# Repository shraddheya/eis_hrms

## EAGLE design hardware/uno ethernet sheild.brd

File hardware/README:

Hardware and firmware goes here

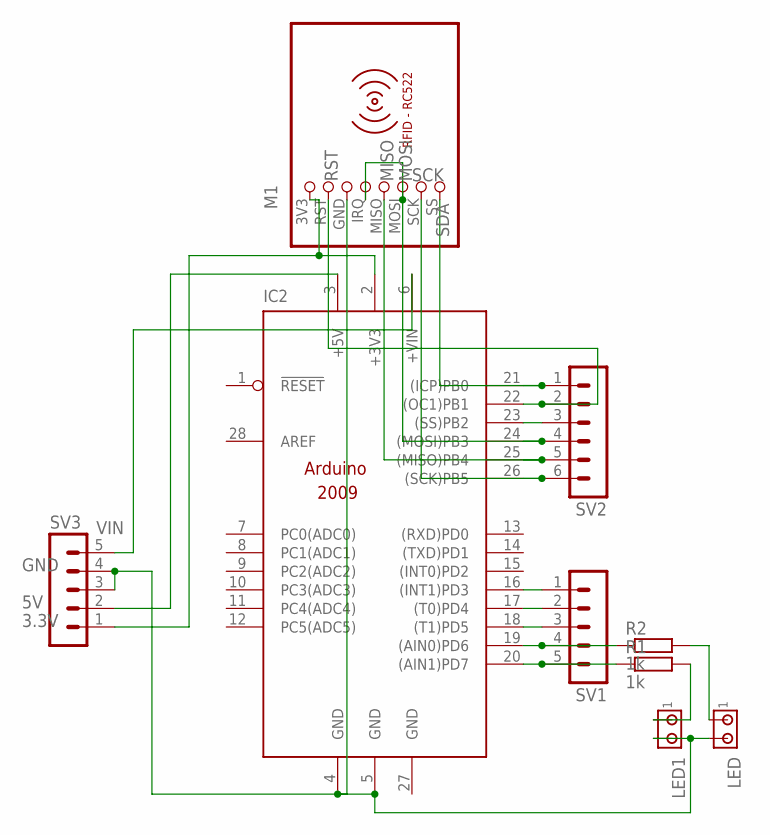
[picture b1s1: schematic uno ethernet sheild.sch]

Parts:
IC2: ARDUINO2009_PIN_12; ARDUINO2009_2
LED, LED1: MTA02-100; 10X02MTA
M1: RFID-RC522
R1, R2: 1k; 0207/10
SV1, SV3: MA05-1
SV2: MA06-1

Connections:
3.3V: IC2.2 (+3V3), M1.3V3 (1), SV3.1
5V: IC2.3 (+5V), SV3.2
GND: IC2.4 (GND), IC2.5 (GND), IC2.27 (GND), LED.2, LED1.2, M1.GND (3), SV3.3, SV3.4
MISO: IC2.25 ((MISO)PB4), M1.MISO (5), SV2.5
MOSI: IC2.24 ((MOSI)PB3), M1.IRQ (4), M1.MOSI (6), SV2.4
unnamed: LED1.1, R1.2
unnamed: LED.1, R2.2
unnamed: IC2.20 ((AIN1)PD7), R1.1, SV1.5
unnamed: IC2.19 ((AIN0)PD6), R2.1, SV1.4
unnamed: IC2.18 ((T1)PD5), SV1.3
unnamed: IC2.17 ((T0)PD4), SV1.2
unnamed: IC2.16 ((INT1)PD3), SV1.1
unnamed: IC2.23 ((SS)PB2), SV2.3
RST: IC2.22 ((OC1)PB1), M1.RST (2), SV2.2
SCK: IC2.26 ((SCK)PB5), M1.SCK (7), SV2.6
SDA: IC2.21 ((ICP)PB0), M1.SS (8), SV2.1
VIN: IC2.6 (+VIN), SV3.5

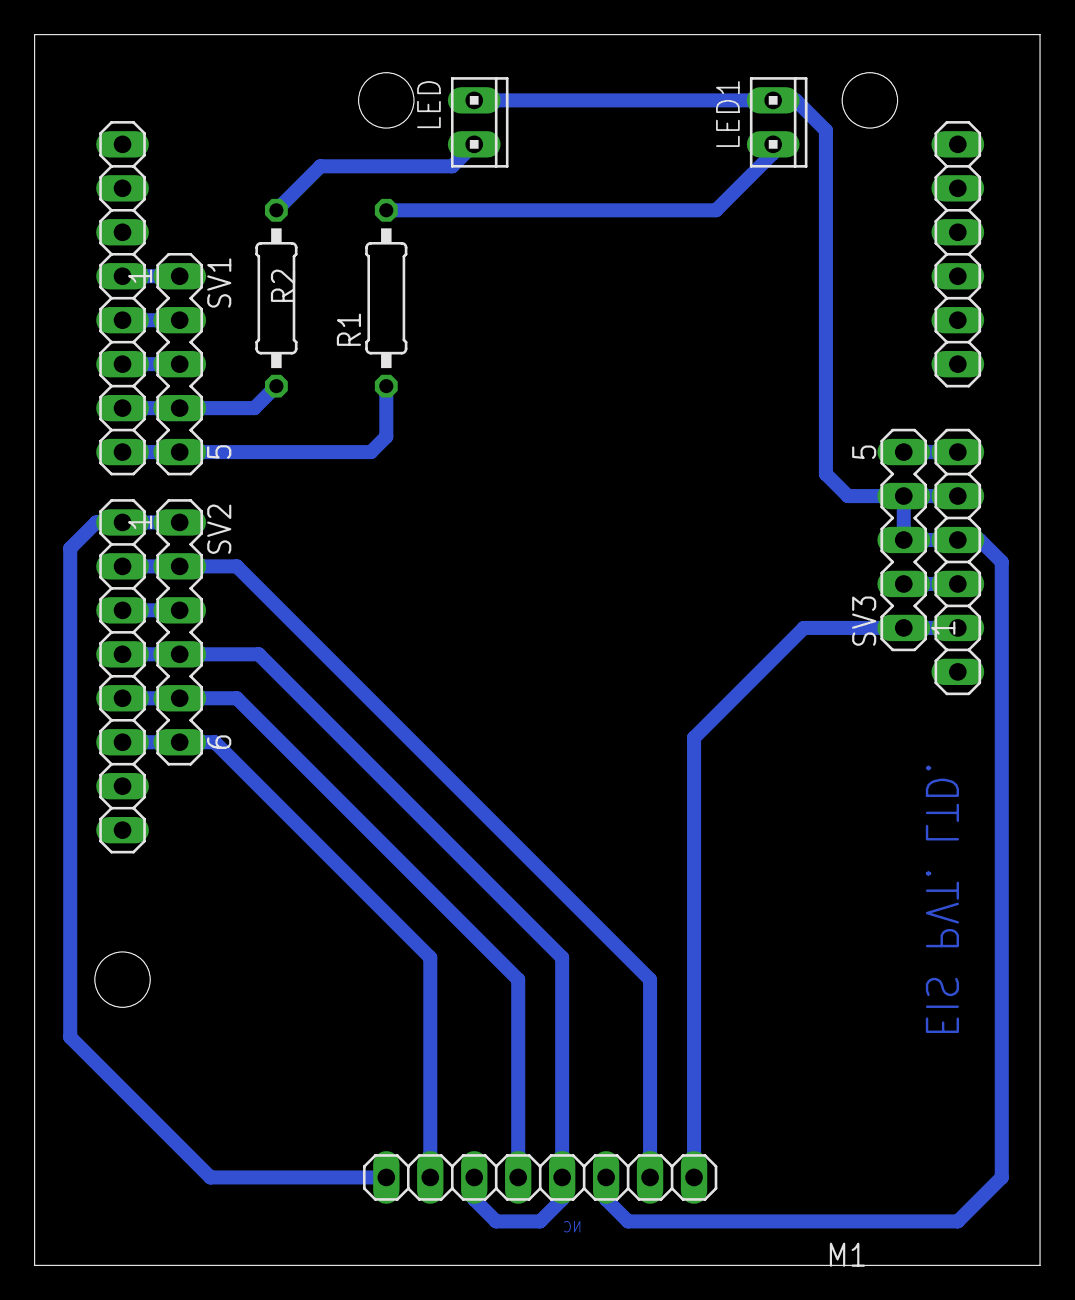
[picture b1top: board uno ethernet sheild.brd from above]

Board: 2 copper layers, 58.1 x 71.1 mm, 9 parts (0 on the bottom side), 17 nets.

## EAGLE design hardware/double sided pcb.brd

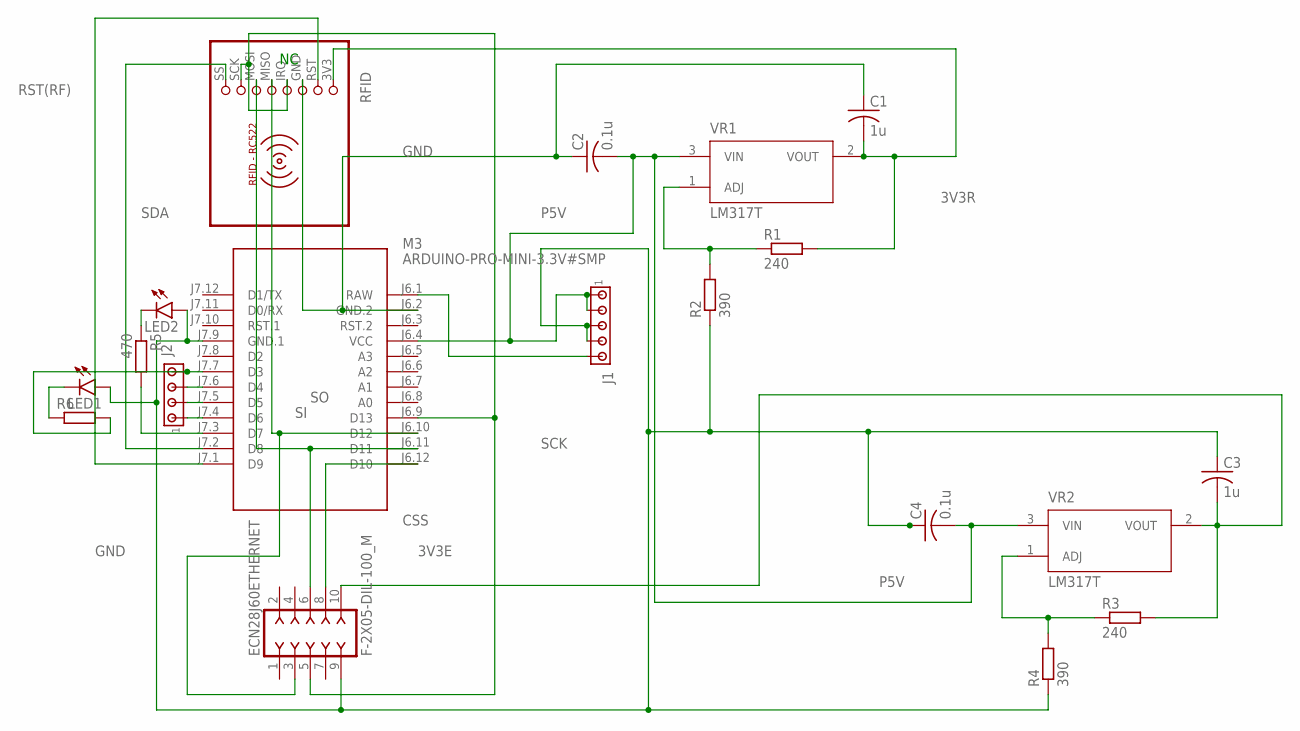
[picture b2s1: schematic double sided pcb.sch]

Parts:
C1, C3: 1u; C025-025X050
C2, C4: 0.1u; C025-025X050
ECN28J60ETHERNET: F-2X05-DIL-100_M; DIL-100-2X05_M
J1: MTA05-100; 10X05MTA
J2: MTA04-100; 10X04MTA
LED1, LED2: LED3MM
M3: ARDUINO-PRO-MINI-3.3V#SMP; ARDUINO-PRO-MINI#SMP
R1, R3: 240; 0207/10
R2, R4: 390; 0207/10
R5: 470; 0207/10
R6: R-EU_0207/10; 0207/10
RFID: RFID-RC522
VR1, VR2: LM317T; TO254P1054X470X1955-3

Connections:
3V3E: C3.2, ECN28J60ETHERNET.10, R3.2, VR2.2 (VOUT)
3V3R: C1.2, R1.2, RFID.3V3 (1), VR1.2 (VOUT)
9V: J1.5, M3.J6.1 (RAW)
CSS: ECN28J60ETHERNET.8, M3.J6.12 (D10)
GND: C1.1, C2.1, C3.1, C4.1, ECN28J60ETHERNET.9, J1.3, J1.4, LED1.A, LED2.A, M3.J6.2 (GND.2), M3.J7.9 (GND.1), R2.1, R4.1, RFID.GND (3)
unnamed: R1.1, R2.2, VR1.1 (ADJ)
unnamed: R3.1, R4.2, VR2.1 (ADJ)
unnamed: J2.3, M3.J7.6 (D4)
unnamed: LED2.K (C), R5.1
unnamed: M3.J7.3 (D7), R5.2
unnamed: J2.1, M3.J7.4 (D6)
unnamed: J2.2, M3.J7.5 (D5)
unnamed: J2.4, M3.J7.7 (D3), R6.2
unnamed: LED1.K (C), R6.1
P5V: C2.2, C4.2, J1.1, J1.2, M3.J6.4 (VCC), VR1.3 (VIN), VR2.3 (VIN)
RST(RF): M3.J7.1 (D9), RFID.RST (2)
SCK: ECN28J60ETHERNET.5, M3.J6.9 (D13), RFID.IRQ (4), RFID.SCK (7)
SDA: M3.J7.2 (D8), RFID.SS (8)
SI: ECN28J60ETHERNET.6, M3.J6.11 (D11), RFID.MOSI (6)
SO: ECN28J60ETHERNET.3, M3.J6.10 (D12), RFID.MISO (5)

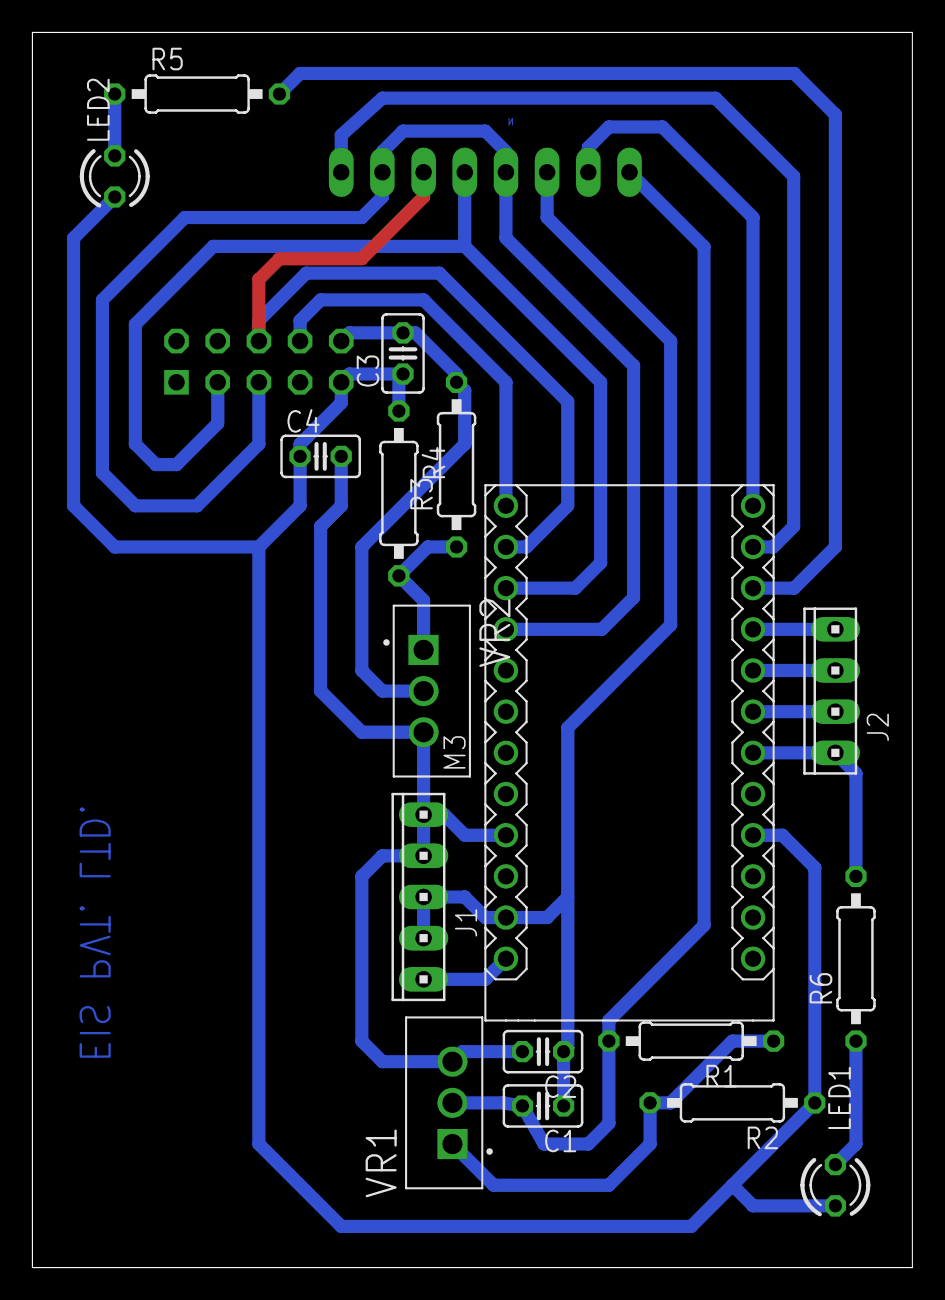
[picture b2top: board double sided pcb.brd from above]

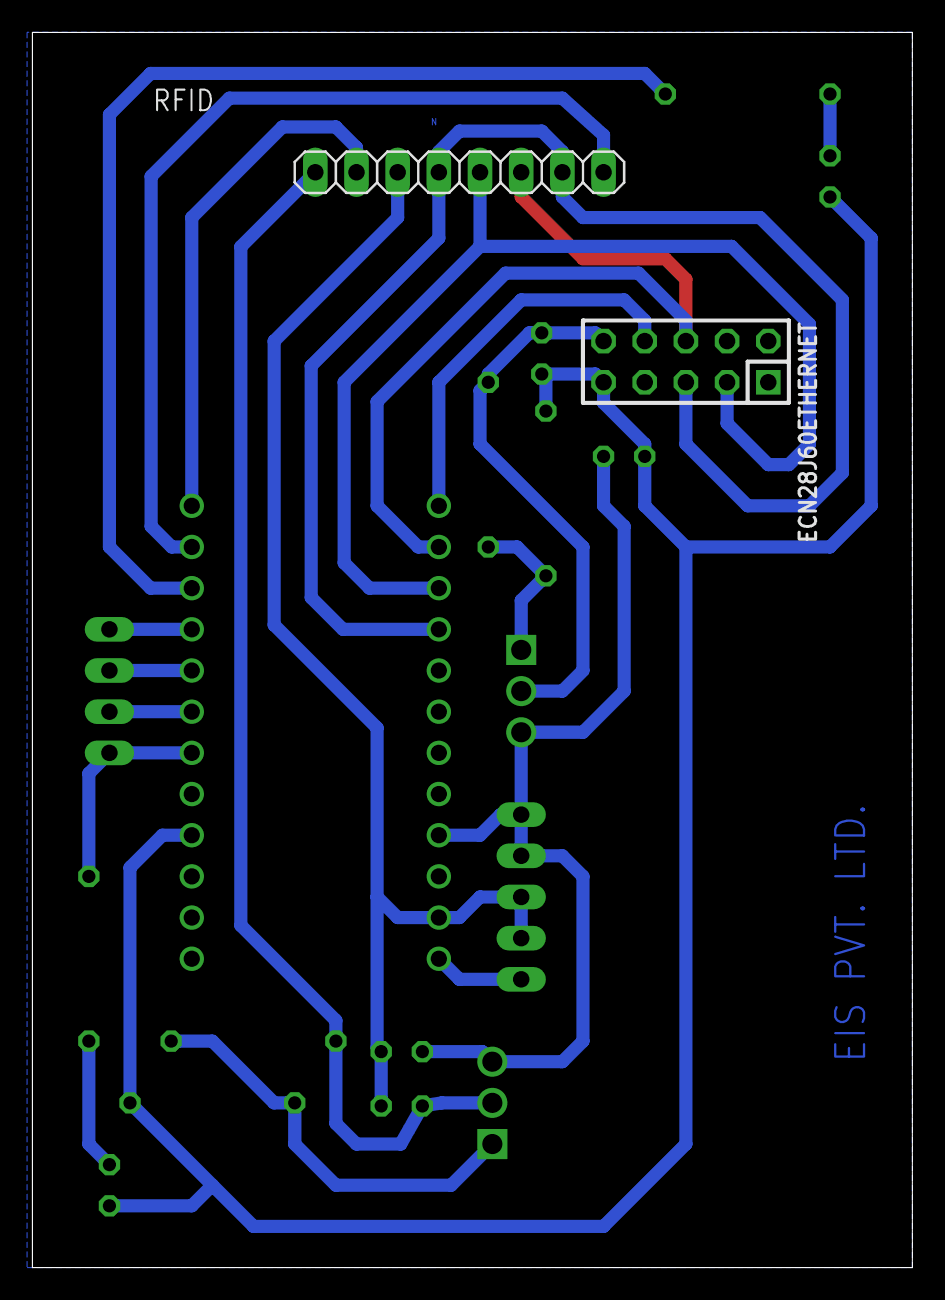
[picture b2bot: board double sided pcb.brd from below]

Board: 2 copper layers, 54.3 x 76.2 mm, 19 parts (2 on the bottom side), 20 nets.

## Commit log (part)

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2020-02-07 initiating first commit
2020-02-10 code commit
2020-02-10 sqldb retained
2020-02-11 frontendchanges
2020-02-11 warningremoved
2020-02-13 php local changes
2020-02-14 latestcode20200214
2020-02-14 cors origin changes
2020-02-14 latest
2020-02-18 db chages
2020-02-18 localCommit
2020-02-19 latestcode20200219
2020-02-19 initiated new pro minute changes
2020-02-20 mysqlDB cleaned
2020-02-20 topnavlogin added
2020-02-20 fewchange
2020-02-20 somechanges
2020-02-21 localchanges
2020-02-22 changes200222
2020-02-24 few changes
2020-02-25 fewchanges portal
2020-02-26 feature of node click
2020-02-27 local commits
2020-02-27 adminpage add record complete
2020-02-28 latestcode200228
2020-03-02 folder changes
2020-03-02 enc28j60 uip_ethernet
2020-03-02 updatedcode200302
2020-03-03 enc28j60 lan module
2020-03-12 latestcode200312
2020-03-13 ENC28J60 LAN MODULE PCB
2020-03-18 UNO ETHERNET PCB for attandance project
2020-04-05 Bump acorn from 6.4.0 to 6.4.1 in /l200207/frontEndCleanShrad
    Bumps [acorn](https://github.com/acornjs/acorn) from 6.4.0 to 6.4.1.
    - [Release notes](https://github.com/acornjs/acorn/releases)
    - [Commits](https://github.com/acornjs/acorn/compare/6.4.0...6.4.1)
2020-04-24 All Changes Backend
2020-04-30 Bump jquery from 3.4.1 to 3.5.0 in /l200213/frontend
    Bumps [jquery](https://github.com/jquery/jquery) from 3.4.1 to 3.5.0.
    - [Release notes](https://github.com/jquery/jquery/releases)
    - [Commits](https://github.com/jquery/jquery/compare/3.4.1...3.5.0)
2020-05-07 google analytics id changed
2020-06-07 Bump websocket-extensions in /l200207/frontEndCleanShrad
    Bumps [websocket-extensions](https://github.com/faye/websocket-extensions-node) from 0.1.3 to 0.1.4.
    - [Release notes](https://github.com/faye/websocket-extensions-node/releases)
    - [Changelog](https://github.com/faye/websocket-extensions-node/blob/master/CHANGELOG.md)
    - [Commits](https://github.com/faye/websocket-extensions-node/compare/0.1.3...0.1.4)
2020-07-19 Bump lodash from 4.17.15 to 4.17.19 in /l200213/frontend
    Bumps [lodash](https://github.com/lodash/lodash) from 4.17.15 to 4.17.19.
    - [Release notes](https://github.com/lodash/lodash/releases)
    - [Commits](https://github.com/lodash/lodash/compare/4.17.15...4.17.19)
2020-08-01 Bump elliptic from 6.5.2 to 6.5.3 in /l200213/frontend
    Bumps [elliptic](https://github.com/indutny/elliptic) from 6.5.2 to 6.5.3.
    - [Release notes](https://github.com/indutny/elliptic/releases)
    - [Commits](https://github.com/indutny/elliptic/compare/v6.5.2...v6.5.3)
2021-03-10 Bump elliptic from 6.5.2 to 6.5.4 in /l200213/frontend
    Bumps [elliptic](https://github.com/indutny/elliptic) from 6.5.2 to 6.5.4.
    - [Release notes](https://github.com/indutny/elliptic/releases)
    - [Commits](https://github.com/indutny/elliptic/compare/v6.5.2...v6.5.4)
2021-03-31 Bump y18n from 4.0.0 to 4.0.1 in /l200213/frontend
    Bumps [y18n](https://github.com/yargs/y18n) from 4.0.0 to 4.0.1.
    - [Release notes](https://github.com/yargs/y18n/releases)
    - [Changelog](https://github.com/yargs/y18n/blob/master/CHANGELOG.md)
    - [Commits](https://github.com/yargs/y18n/commits)
2021-04-30 Bump ssri from 6.0.1 to 6.0.2 in /l200207/frontEndCleanShrad
    Bumps [ssri](https://github.com/npm/ssri) from 6.0.1 to 6.0.2.
    - [Release notes](https://github.com/npm/ssri/releases)
    - [Changelog](https://github.com/npm/ssri/blob/v6.0.2/CHANGELOG.md)
    - [Commits](https://github.com/npm/ssri/compare/v6.0.1...v6.0.2)
2021-05-09 Bump url-parse from 1.4.7 to 1.5.1 in /l200207/frontEndCleanShrad
    Bumps [url-parse](https://github.com/unshiftio/url-parse) from 1.4.7 to 1.5.1.
    - [Release notes](https://github.com/unshiftio/url-parse/releases)
    - [Commits](https://github.com/unshiftio/url-parse/compare/1.4.7...1.5.1)
2021-05-11 Bump hosted-git-info from 2.8.5 to 2.8.9 in /l200213/frontend
    Bumps [hosted-git-info](https://github.com/npm/hosted-git-info) from 2.8.5 to 2.8.9.
    - [Release notes](https://github.com/npm/hosted-git-info/releases)
    - [Changelog](https://github.com/npm/hosted-git-info/blob/v2.8.9/CHANGELOG.md)
    - [Commits](https://github.com/npm/hosted-git-info/compare/v2.8.5...v2.8.9)
2021-05-12 Bump chart.js from 2.9.3 to 2.9.4 in /l200207/frontEndCleanShrad
    Bumps [chart.js](https://github.com/chartjs/Chart.js) from 2.9.3 to 2.9.4.
    - [Release notes](https://github.com/chartjs/Chart.js/releases)
    - [Commits](https://github.com/chartjs/Chart.js/compare/v2.9.3...v2.9.4)
2021-05-28 Bump dns-packet from 1.3.1 to 1.3.4 in /l200207/frontEndCleanShrad
    Bumps [dns-packet](https://github.com/mafintosh/dns-packet) from 1.3.1 to 1.3.4.
    - [Release notes](https://github.com/mafintosh/dns-packet/releases)
    - [Changelog](https://github.com/mafintosh/dns-packet/blob/master/CHANGELOG.md)
    - [Commits](https://github.com/mafintosh/dns-packet/compare/v1.3.1...v1.3.4)
2021-08-04 Bump tar from 4.4.13 to 4.4.15 in /l200207/frontEndCleanShrad
    Bumps [tar](https://github.com/npm/node-tar) from 4.4.13 to 4.4.15.
    - [Release notes](https://github.com/npm/node-tar/releases)
    - [Changelog](https://github.com/npm/node-tar/blob/main/CHANGELOG.md)
    - [Commits](https://github.com/npm/node-tar/compare/v4.4.13...v4.4.15)
    ---
    updated-dependencies:
2021-09-02 Bump tar from 4.4.13 to 4.4.19 in /l200213/frontend
    Bumps [tar](https://github.com/npm/node-tar) from 4.4.13 to 4.4.19.
    - [Release notes](https://github.com/npm/node-tar/releases)
    - [Changelog](https://github.com/npm/node-tar/blob/main/CHANGELOG.md)
    - [Commits](https://github.com/npm/node-tar/compare/v4.4.13...v4.4.19)
    ---
    updated-dependencies:
2021-10-06 Bump url-parse from 1.4.7 to 1.5.3 in /l200213/frontend
    Bumps [url-parse](https://github.com/unshiftio/url-parse) from 1.4.7 to 1.5.3.
    - [Release notes](https://github.com/unshiftio/url-parse/releases)
    - [Commits](https://github.com/unshiftio/url-parse/compare/1.4.7...1.5.3)
    ---
    updated-dependencies:
    - dependency-name: url-parse
2022-02-11 Bump karma from 4.1.0 to 6.3.14 in /l200213/frontend
    Bumps [karma](https://github.com/karma-runner/karma) from 4.1.0 to 6.3.14.
    - [Release notes](https://github.com/karma-runner/karma/releases)
    - [Changelog](https://github.com/karma-runner/karma/blob/master/CHANGELOG.md)
    - [Commits](https://github.com/karma-runner/karma/compare/v4.1.0...v6.3.14)
    ---
    updated-dependencies:
2022-02-13 Bump follow-redirects from 1.10.0 to 1.14.8 in /l200213/frontend
    Bumps [follow-redirects](https://github.com/follow-redirects/follow-redirects) from 1.10.0 to 1.14.8.
    - [Release notes](https://github.com/follow-redirects/follow-redirects/releases)
    - [Commits](https://github.com/follow-redirects/follow-redirects/compare/v1.10.0...v1.14.8)
    ---
    updated-dependencies:
    - dependency-name: follow-redirects
2022-02-26 Bump url-parse from 1.4.7 to 1.5.10 in /l200213/frontend
    Bumps [url-parse](https://github.com/unshiftio/url-parse) from 1.4.7 to 1.5.10.
    - [Release notes](https://github.com/unshiftio/url-parse/releases)
    - [Commits](https://github.com/unshiftio/url-parse/compare/1.4.7...1.5.10)
    ---
    updated-dependencies:
    - dependency-name: url-parse
2022-03-02 Bump karma from 4.1.0 to 6.3.16 in /l200213/frontend
    Bumps [karma](https://github.com/karma-runner/karma) from 4.1.0 to 6.3.16.
    - [Release notes](https://github.com/karma-runner/karma/releases)
    - [Changelog](https://github.com/karma-runner/karma/blob/master/CHANGELOG.md)
    - [Commits](https://github.com/karma-runner/karma/compare/v4.1.0...v6.3.16)
    ---
    updated-dependencies:
2022-04-09 Bump moment from 2.24.0 to 2.29.2 in /l200213/frontend
    Bumps [moment](https://github.com/moment/moment) from 2.24.0 to 2.29.2.
    - [Release notes](https://github.com/moment/moment/releases)
    - [Changelog](https://github.com/moment/moment/blob/develop/CHANGELOG.md)
    - [Commits](https://github.com/moment/moment/compare/2.24.0...2.29.2)
    ---
    updated-dependencies:
2022-06-01 Bump eventsource from 1.0.7 to 1.1.1 in /l200213/frontend
    Bumps [eventsource](https://github.com/EventSource/eventsource) from 1.0.7 to 1.1.1.
    - [Release notes](https://github.com/EventSource/eventsource/releases)
    - [Changelog](https://github.com/EventSource/eventsource/blob/master/HISTORY.md)
    - [Commits](https://github.com/EventSource/eventsource/compare/v1.0.7...v1.1.1)
    ---
    updated-dependencies:
2022-06-03 Bump @angular/core from 8.2.14 to 11.0.5 in /l200207/frontEndCleanShrad
    Bumps [@angular/core](https://github.com/angular/angular/tree/HEAD/packages/core) from 8.2.14 to 11.0.5.
    - [Release notes](https://github.com/angular/angular/releases)
    - [Changelog](https://github.com/angular/angular/blob/main/CHANGELOG.md)
    - [Commits](https://github.com/angular/angular/commits/11.0.5/packages/core)
    ---
    updated-dependencies:
2022-07-07 Bump moment from 2.24.0 to 2.29.4 in /l200213/frontend
    Bumps [moment](https://github.com/moment/moment) from 2.24.0 to 2.29.4.
    - [Release notes](https://github.com/moment/moment/releases)
    - [Changelog](https://github.com/moment/moment/blob/develop/CHANGELOG.md)
    - [Commits](https://github.com/moment/moment/compare/2.24.0...2.29.4)
    ---
    updated-dependencies:
2022-11-19 Bump loader-utils and @angular-devkit/build-angular in /l200213/frontend
    Bumps [loader-utils](https://github.com/webpack/loader-utils) to 3.2.1 and updates ancestor dependency [@angular-devkit/build-angular](https://github.com/angular/angular-cli). These dependencies need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
    Updates `loader-utils` from 1.2.3 to 3.2.1
    - [Release notes](https://github.com/webpack/loader-utils/releases)
    - [Changelog](https://github.com/webpack/loader-utils/blob/master/CHANGELOG.md)
    - [Commits](https://github.com/webpack/loader-utils/compare/v1.2.3...v3.2.1)
    Updates `@angular-devkit/build-angular` from 0.803.25 to 15.0.0
2022-11-23 Bump engine.io and karma in /l200213/frontend
    Bumps [engine.io](https://github.com/socketio/engine.io) to 6.2.1 and updates ancestor dependency [karma](https://github.com/karma-runner/karma). These dependencies need to be updated together.
    Updates `engine.io` from 3.2.1 to 6.2.1
    - [Release notes](https://github.com/socketio/engine.io/releases)
    - [Changelog](https://github.com/socketio/engine.io/blob/main/CHANGELOG.md)
    - [Commits](https://github.com/socketio/engine.io/compare/3.2.1...6.2.1)
    Updates `karma` from 4.1.0 to 6.4.1
2022-12-05 Bump decode-uri-component in /l200207/frontEndCleanShrad
    Bumps [decode-uri-component](https://github.com/SamVerschueren/decode-uri-component) from 0.2.0 to 0.2.2.
    - [Release notes](https://github.com/SamVerschueren/decode-uri-component/releases)
    - [Commits](https://github.com/SamVerschueren/decode-uri-component/compare/v0.2.0...v0.2.2)
    ---
    updated-dependencies:
    - dependency-name: decode-uri-component
2022-12-12 Bump express from 4.17.1 to 4.18.2 in /l200213/frontend
    Bumps [express](https://github.com/expressjs/express) from 4.17.1 to 4.18.2.
    - [Release notes](https://github.com/expressjs/express/releases)
    - [Changelog](https://github.com/expressjs/express/blob/master/History.md)
    - [Commits](https://github.com/expressjs/express/compare/4.17.1...4.18.2)
    ---
    updated-dependencies:
2023-01-01 Bump json5 and @angular-devkit/build-angular
    Bumps [json5](https://github.com/json5/json5) to 2.2.3 and updates ancestor dependency [@angular-devkit/build-angular](https://github.com/angular/angular-cli). These dependencies need to be updated t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
    Updates `json5` from 1.0.1 to 2.2.3
    - [Release notes](https://github.com/json5/json5/releases)
    - [Changelog](https://github.com/json5/json5/blob/main/CHANGELOG.md)
    - [Commits](https://github.com/json5/json5/compare/v1.0.1...v2.2.3)
    Updates `@angular-devkit/build-angular` from 0.803.25 to 15.0.4

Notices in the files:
parts and their libraries:
con-headers-jp: Copyright (C) 2008, Bob Starr
diy-modules: Released under the Creative Commons Attribution 4.0 International License: http://creativecommons.org/licenses/by/4.0
